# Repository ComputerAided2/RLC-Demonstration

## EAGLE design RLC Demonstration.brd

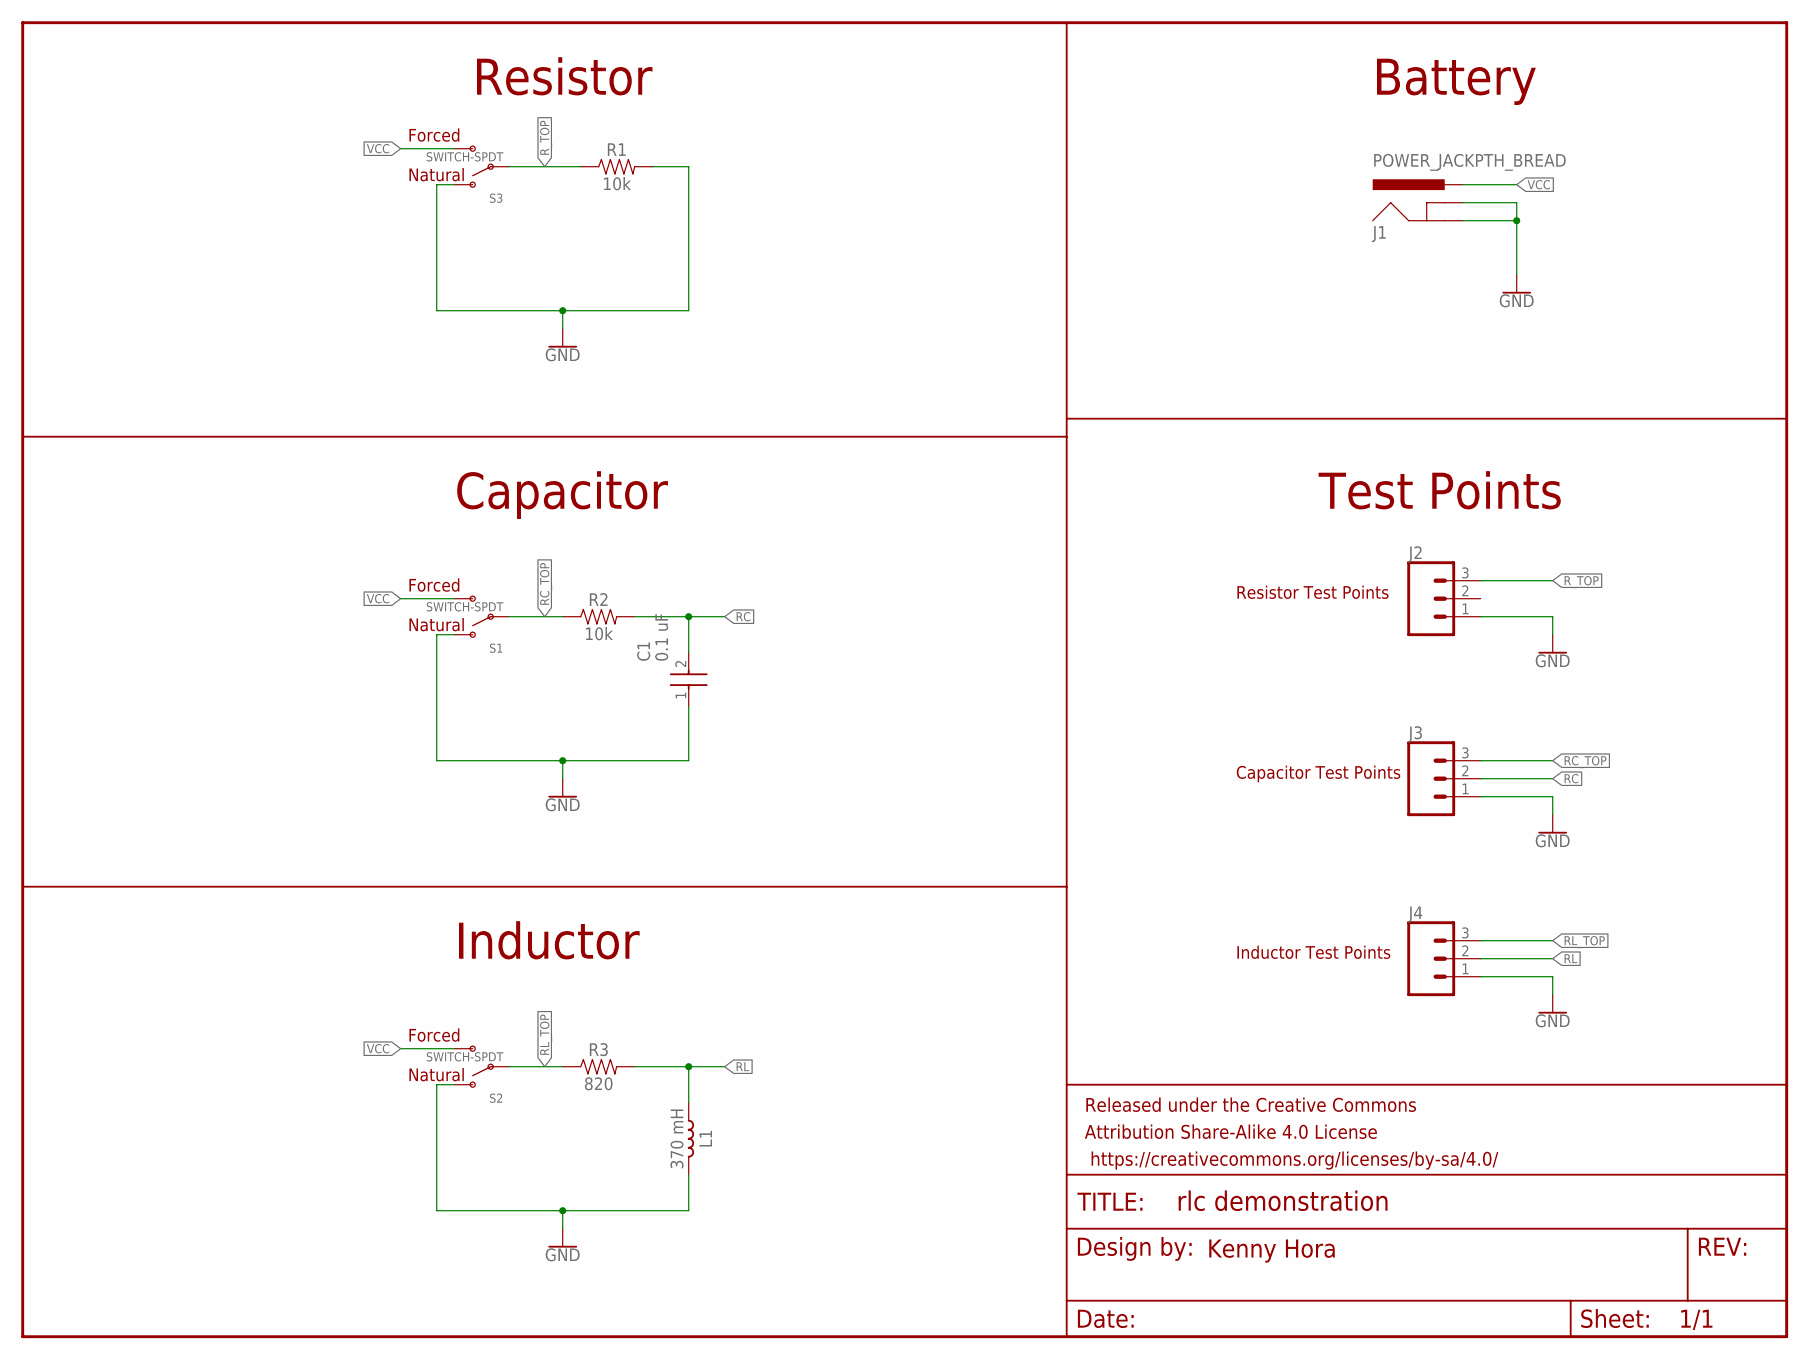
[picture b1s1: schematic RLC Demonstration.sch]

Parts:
C1: 0.1 uF; K104K15X7RF53H5
FRAME1: FRAME-LETTERNO_PACKAGE; DUMMY
J1: POWER_JACKPTH_BREAD; POWER_JACK_PTH_BREAD
J2, J3, J4: CONN_03LOCK; 1X03_LOCK
L1: 370 mH; KNOWLES-5100-253441
R1, R2: 10k; AXIAL-0.3
R3: 820; AXIAL-0.3
S1, S2, S3: SWITCH-SPDT; OS102011MA1QN1

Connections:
GND: C1.1, J1.GND, J1.GNDBREAK, J2.1, J3.1, J4.1, L1.P$1, R1.P$2 (2), S1.P$2, S2.P$2, S3.P$2
RC: C1.2, J3.2, R2.P$2 (2)
RC_TOP: J3.3, R2.P$1 (1), S1.P$1
RL: J4.2, L1.P$2, R3.P$2 (2)
RL_TOP: J4.3, R3.P$1 (1), S2.P$1
R_TOP: J2.3, R1.P$1 (1), S3.P$1
VCC: J1.PWR, S1.P$3, S2.P$3, S3.P$3

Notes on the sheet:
Kenny Hora
Battery
Resistor
Capacitor
Inductor
Forced
Natural
Test Points
Resistor Test Points
Capacitor Test Points
Inductor Test Points

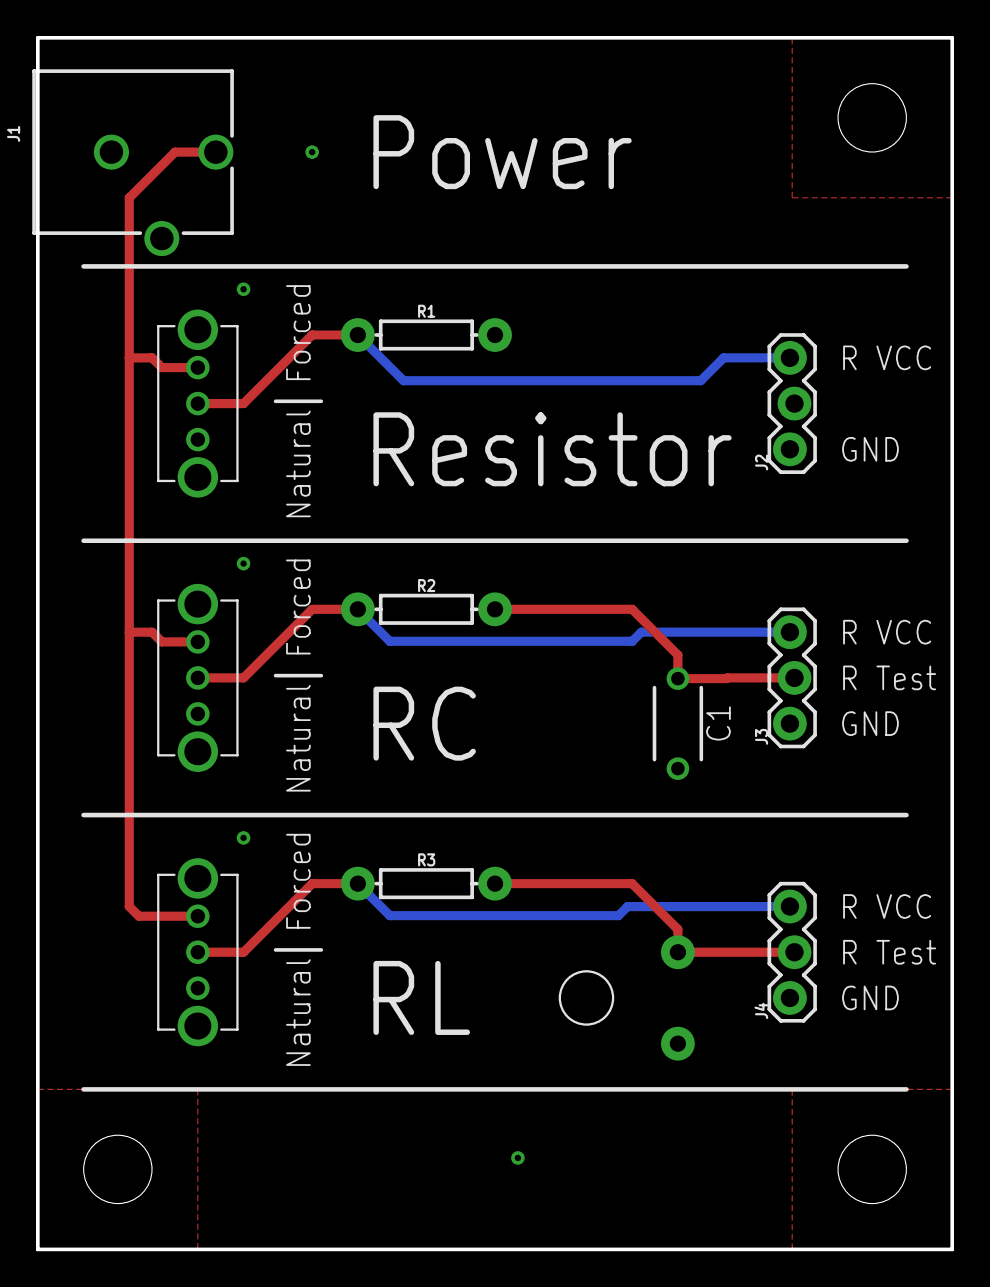
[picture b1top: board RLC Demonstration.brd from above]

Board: 2 copper layers, 50.8 x 67.3 mm, 13 parts (0 on the bottom side), 7 nets.

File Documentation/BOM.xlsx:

Qty Per Board | Qty Total | Value | Parts | Part Link | Unit Cost | Total Cost
3 | 15 | n/a | J2, J3, J4 | n/a | 0 | 0
1 | 5 | 0.1 uF | C1 | https://www.mouser.com/ProductDetail/594-K104K15X7RF53H5 | 0.1 | 0.5
2 | 10 | 10k | R1, R2 | https://www.mouser.com/ProductDetail/603-CFR-25JT-52-10K | 4.5999999999999999E-2 | 0.45999999999999996
1 | 5 | 370 mH | L1 | https://www.mouser.com/ProductDetail/721-5100253441 | 5.01 | 25.049999999999997
1 | 5 | 820 Ω | R3 | https://www.mouser.com/ProductDetail/603-CFR-25JT-52-820R | 0.1 | 0.5
1 | 5 | FRAME-LETTERNO_PACKAGE | FRAME1 | n/a | 0 | 0
1 | 5 | POWER_JACKPTH_BREAD | J1 | https://www.mouser.com/ProductDetail/474-PRT-10811 | 0.95 | 4.75
3 | 15 | SWITCH-SPDT | S1, S2, S3 | https://www.mouser.com/ProductDetail/611-OS102011MA1QN1 | 0.373 | 5.5949999999999998
 |  |  |  |  | Total: | 36.854999999999997

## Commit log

2020-10-04 Add .gitignore
2020-10-10 Create Calculations.xlsx
    Create spreadsheet page to calculate timing and power dissipation of the various circuits.
2020-10-10 Update schematic
    Remove extra circuits from schematic and calculate values to put response times in the millisecond range.
2020-10-10 Removed erroneous current measurement jumper.
2020-11-05 Update Part Values
2020-11-25 Finalize Board Designs
    Changed sch drawings to actual parts and routed board.
2020-11-25 Move schematics to own folder
    Move schematics to own folder
2020-11-25 Export Gerber Files
    Exported Gerber files in both zipped and unzipped format
2020-11-25 Create and Move Documentation to own folder
    Create and Move Documentation to own folder

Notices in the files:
parts and their libraries:
SparkFun-Aesthetics: Licensing: Creative Commons ShareAlike 4.0 International - https://creativecommons.org/licenses/by-sa/4.0
SparkFun-Aesthetics: Released under the Creative Commons Attribution Share-Alike 4.0 License
SparkFun-Aesthetics: https://creativecommons.org/licenses/by-sa/4.0
